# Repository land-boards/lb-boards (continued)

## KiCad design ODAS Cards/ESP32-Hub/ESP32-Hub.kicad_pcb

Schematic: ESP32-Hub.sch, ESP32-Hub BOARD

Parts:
C2, C4, C5, C6: 0.1uF; C_0805_HandSoldering
C3: 10uF; C_1206_HandSoldering
F1: Polyfuse_Small; Fuse_1206_3216Metric_Pad1.42x1.75mm_HandSolder
H1: Conn_01x02; PinHeader_1x02_P2.54mm_Vertical
H2: Conn_02x03_Odd_Even; PinHeader_2x03_P2.54mm_Vertical
J1: DCJ0202; DCJ-NEW
J2: FTDI; Pin_Header_Straight_1x06_Pitch2.54mm
J3: Conn_02x03_Odd_Even; Pin_Header_Straight_2x03_Pitch2.54mm
J4, J5, J6, J8: Conn_01x03; Pin_Header_Straight_1x03_Pitch2.54mm
J7, J9, J10, J11, J12: Conn_01x05; Pin_Header_Straight_1x05_Pitch2.54mm
J15: Conn_01x02; TB2-5MM
MTG1, MTG2, MTG3: MTG_HOLE; MTG-6-32
MTG?1: MTG_HOLE; MTG-6-32
P1: Conn_02x08_Odd_Even; Pin_Header_Straight_2x08_Pitch2.54mm
P2, P11: Conn_02x14_Odd_Even; Pin_Header_Straight_2x14_Pitch2.54mm
P8: Conn_02x03_Odd_Even; Pin_Header_Straight_2x03_Pitch2.54mm
P12, P13: Conn_01x14; Pin_Header_Straight_1x14_Pitch2.54mm
R1, R3, R7, R8, R10, R11, R13, R14, R16, R17: 2.2K; R_0805_HandSoldering
R2, R4, R5, R6, R9, R12, R15, R18: 10K; R_0805_HandSoldering
TEST1: COUPON; TEST_BLK-REAR
U1: ESP32; ESP32_EXP
U2: AP1117; SOT223
U3: TCA9544A; TSSOP-20_4.4x6.5mm_Pitch0.65mm

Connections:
+3V3: C4.1, C5.1, F1.1, J4.1, J5.1, J6.1, J7.4, J8.1, P2.2, P2.4, P2.6, P2.8, P2.10, P2.12, P2.14, P2.16, P2.18, P2.20, P2.22, P2.24, P2.26, P2.28, P8.2, P11.2, P11.4, P11.6, P11.8, P11.10, P11.12, P11.14, P11.16, P11.18, P11.20, P11.22, P11.24, P11.26, P11.28, R1.1, R2.1, R3.1, R4.1, R5.1, R6.1, U3.20 (VCC)
+5V: C6.1, H2.2, H2.4, H2.6, J4.3, J5.3, J6.3, J8.3, P1.2, P1.4, P1.6, P1.8, P1.10, P1.12, P1.14, P1.16, U2.3 (VIN)
/A0: J3.5, R4.2, U3.1 (A0)
/A1: J3.3, R5.2, U3.2 (A1)
/A2: J3.1, R6.2, U3.3 (A2)
/DCIN: H2.3, J1.1, J15.1
/EN: P13.14, U1.16 (EN)
/FTDI5V: H2.5, J2.3 (VCC)
/GP2: P12.3, U1.4 (GP2)
/GP4: P12.4, U1.5 (GP4)
/GP5: J7.1, P12.7, R3.2, U1.8 (GP5), U3.17 (~INT)
/GP12: P13.3, U1.27 (GP12)
/GP13: P13.2, U1.28 (GP13)
/GP14: P13.4, U1.26 (GP14)
/GP15: P12.2, U1.3 (GP15)
/GP18: P8.3, P12.8, U1.9 (GP18/SCK)
/GP19: P8.1, P12.9, U1.10 (GP19/MISO)
/GP23: P8.4, P12.14, U1.15 (GP23/MOSI)
/GP25: P13.7, U1.23 (A8/GPI25)
/GP26: P13.6, U1.24 (A9/GPI26)
/GP27: P13.5, U1.25 (GP27)
/GP32: P13.9, U1.21 (A4/GPI32)
/GP33: P13.8, U1.22 (A5/GPI33)
/GP34: P13.11, U1.19 (A6/GPI34)
/GP35: P13.10, U1.20 (A7/GPI35)
/INT0: J9.5, R9.2, U3.4 (~INT0)
/INT1: J10.5, R12.2, U3.7 (~INT1)
/INT2: J12.5, R15.2, U3.11 (~INT2)
/INT3: J11.5, R18.2, U3.14 (~INT3)
/RX0: J2.4 (TX), P12.11, U1.12 (RX0)
/RX1: P12.5, U1.6 (RX1)
/SC0: J9.4, R7.2, U3.6 (SC0)
/SC1: J10.4, R10.2, U3.9 (SC1)
/SC2: J12.4, R13.2, U3.13 (SC2)
/SC3: J11.4, U3.16 (SC3)
/SD0: J9.3, R8.2, U3.5 (SD0)
/SD1: J10.3, R11.2, U3.8 (SD1)
/SD2: J12.3, R14.2, U3.12 (SD2)
/SD3: J11.3, U3.15 (SD3)
/STM_SCL: J7.2, P12.13, R2.2, U1.14 (GP22/I2CSCL), U3.18 (SCL)
/STM_SDA: J7.3, P12.10, R1.2, U1.11 (GP21/I2CSDA), U3.19 (SDA)
/TX0: J2.5 (RX), P12.12, U1.13 (TX0)
/TX2: P12.6, U1.7 (TX2)
/VN: P13.12, U1.18 (VN)
/VO3: C2.1, C3.1, H1.1, U2.2 (VO), U2.4 (VO)
/VP: P13.13, U1.17 (VP)
/VUSB: H2.1, P13.1, U1.30 (VIN)
GND: C2.2, C3.2, C4.2, C5.2, C6.2, J1.2, J1.3, J2.1 (GND), J3.2, J3.4, J3.6, J7.5, J9.1, J10.1, J11.1, J12.1, J15.2, P1.1, P1.3, P1.5, P1.7, P1.9, P1.11, P1.13, P1.15, P2.1, P2.3, P2.5, P2.7, P2.9, P2.11, P2.13, P2.15, P2.17, P2.19, P2.21, P2.23, P2.25, P2.27, P8.6, P11.1, P11.3, P11.5, P11.7, P11.9, P11.11, P11.13, P11.15, P11.17, P11.19, P11.21, P11.23, P11.25, P11.27, U1.2 (GND), U1.29 (GND), U2.1 (GND), U3.10 (GND)
unnamed: F1.2, H1.2
unnamed: J4.2, J9.2, R7.1, R8.1, R9.1
unnamed: J5.2, J10.2, R10.1, R11.1, R12.1
unnamed: J8.2, J11.2, R16.1, R17.1, R18.1
unnamed: J6.2, J12.2, R13.1, R14.1, R15.1
unnamed: P12.1, U1.1 (3.3V)

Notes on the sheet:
FTDI CONNECTOR
SPI BUS
MISO
SCK
MOSI
I2C BUS

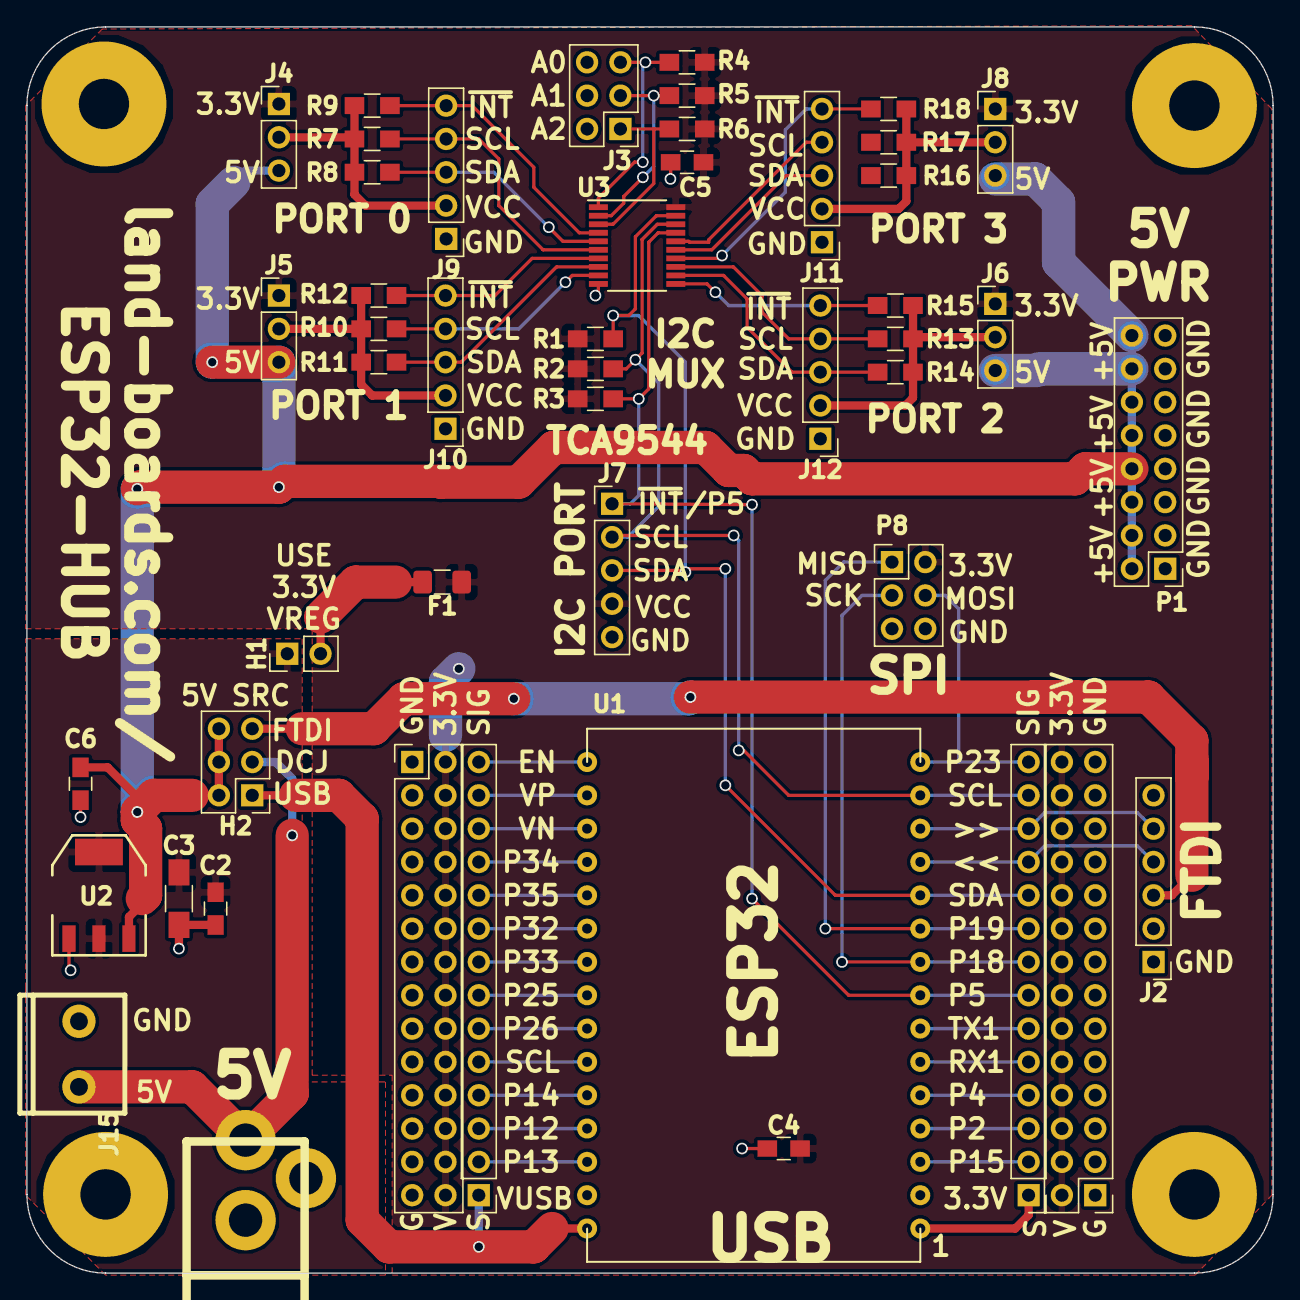
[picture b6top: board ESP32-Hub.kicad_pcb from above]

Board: 2 copper layers, 95.0 x 95.0 mm, 52 parts (0 on the bottom side), 54 nets.
